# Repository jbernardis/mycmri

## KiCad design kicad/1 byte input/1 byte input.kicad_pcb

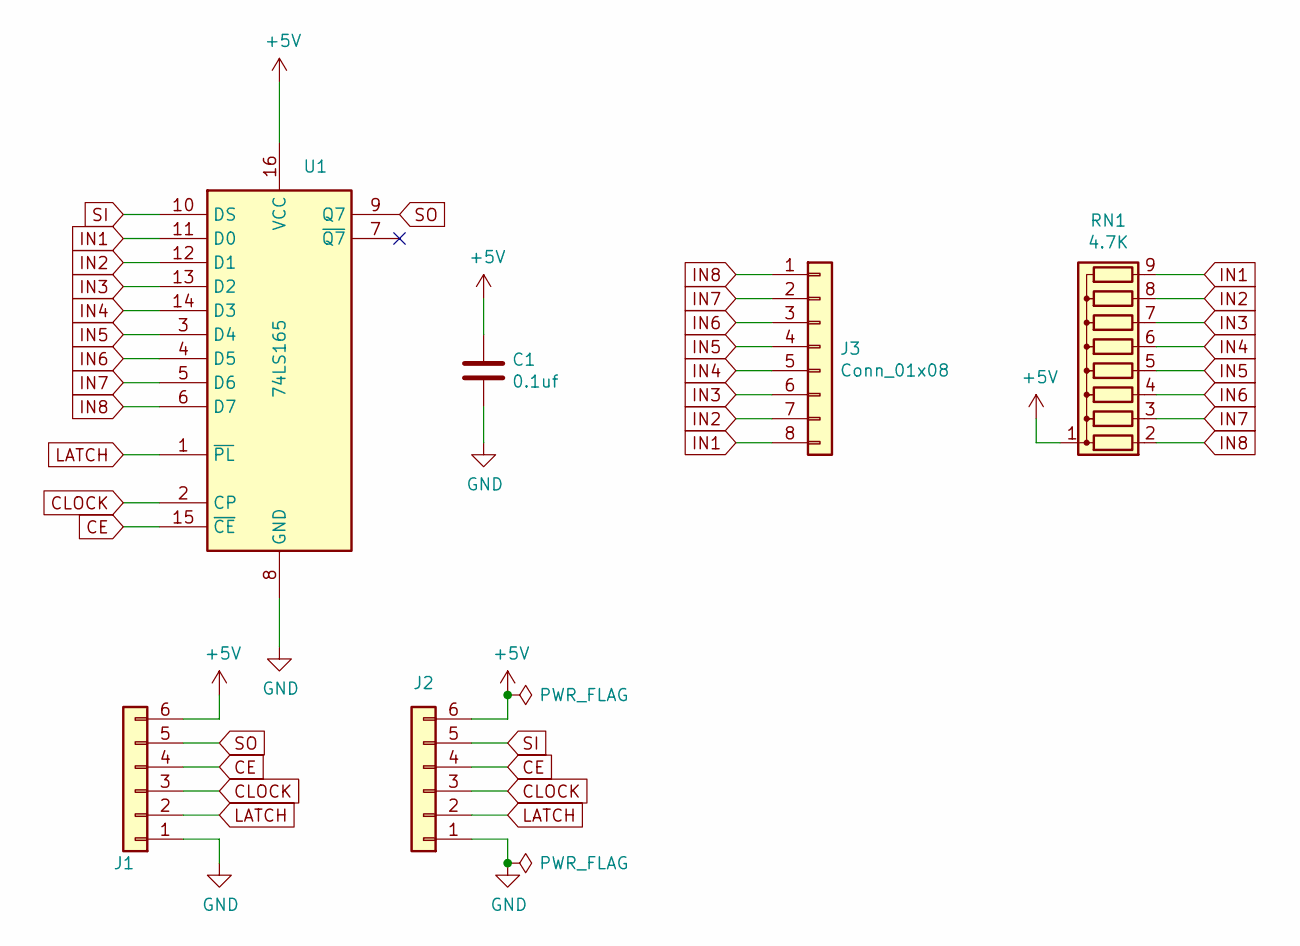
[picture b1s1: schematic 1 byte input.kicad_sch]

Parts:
C1: 0.1uf; C_Disc_D5.0mm_W2.5mm_P2.50mm
J1: Conn_01x06; PinHeader_1x06_P2.54mm_Horizontal
J2: Conn_01x06; PinSocket_1x06_P2.54mm_Horizontal
J3: Conn_01x08; TerminalBlock_Phoenix_MKDS-1,5-8-5.08_1x08_P5.08mm_Horizont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
RN1: 4.7K; R_Array_SIP9
U1: 74LS165; DIP-16_W7.62mm

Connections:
+5V: C1.1, J1.6, J2.6, RN1.1 (common), U1.16 (VCC)
CE: J1.4, J2.4, U1.15 (~CE)
CLOCK: J1.3, J2.3, U1.2 (CP)
GND: C1.2, J1.1, J2.1, U1.8 (GND)
IN1: J3.8, RN1.9 (R8), U1.11 (D0)
IN2: J3.7, RN1.8 (R7), U1.12 (D1)
IN3: J3.6, RN1.7 (R6), U1.13 (D2)
IN4: J3.5, RN1.6 (R5), U1.14 (D3)
IN5: J3.4, RN1.5 (R4), U1.3 (D4)
IN6: J3.3, RN1.4 (R3), U1.4 (D5)
IN7: J3.2, RN1.3 (R2), U1.5 (D6)
IN8: J3.1, RN1.2 (R1), U1.6 (D7)
LATCH: J1.2, J2.2, U1.1 (~PL)
SI: J2.5, U1.10 (DS)
SO: J1.5, U1.9 (Q7)

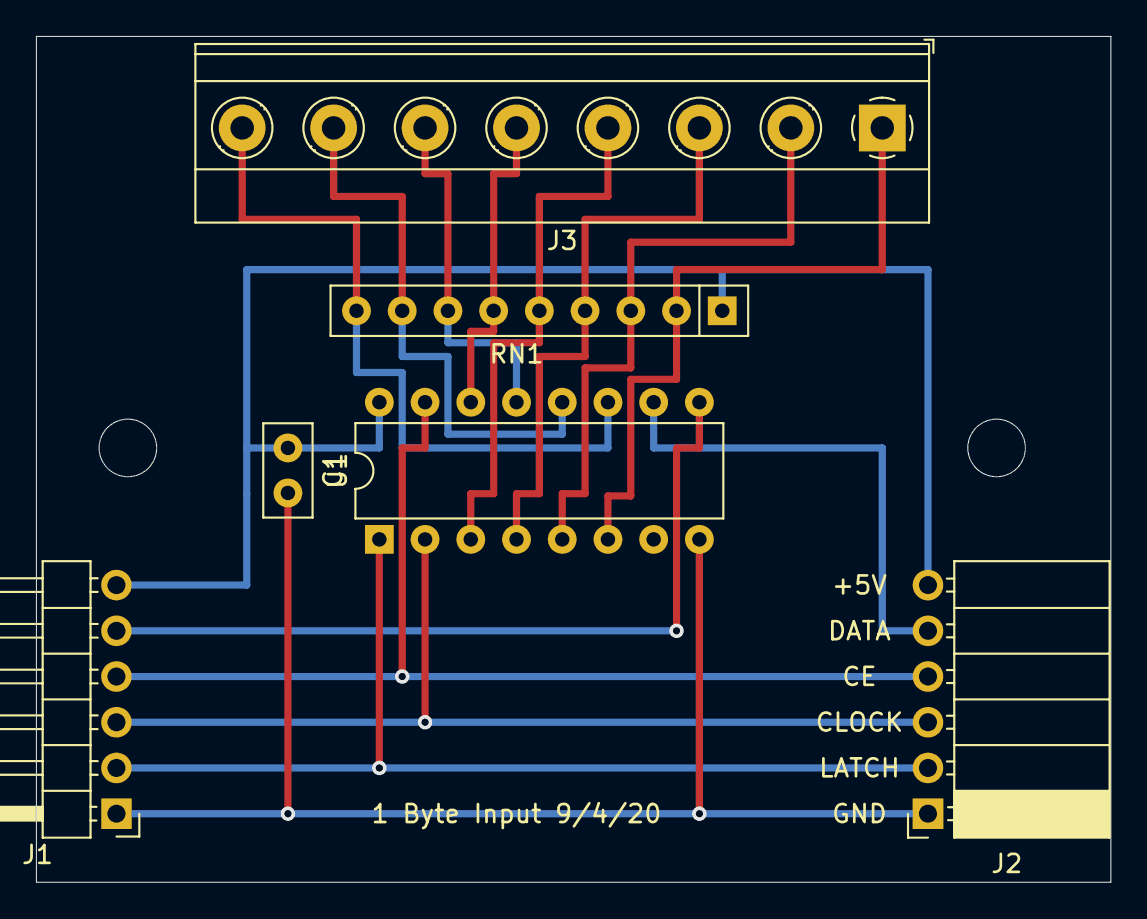
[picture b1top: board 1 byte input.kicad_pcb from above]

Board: 2 copper layers, 59.7 x 47.0 mm, 6 parts (0 on the bottom side), 15 nets.

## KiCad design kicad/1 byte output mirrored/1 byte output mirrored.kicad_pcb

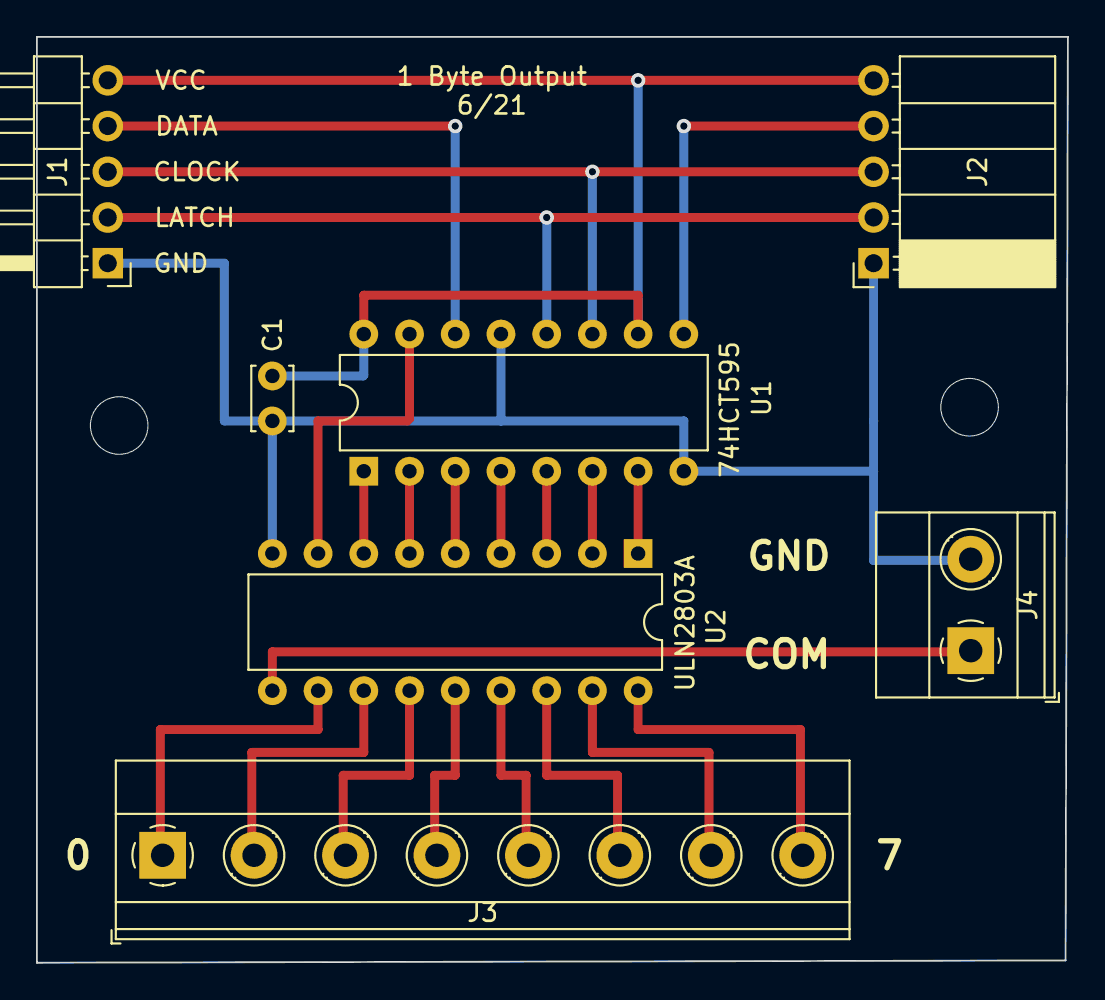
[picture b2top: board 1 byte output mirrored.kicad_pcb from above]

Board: 2 copper layers, 57.3 x 51.4 mm, 9 parts (0 on the bottom side), 23 nets.

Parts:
 : MountingHole_3.2mm_M3
 #2: MountingHole_3.2mm_M3
C1: 0.1uf; C_Disc_D3.4mm_W2.1mm_P2.50mm
J1: Conn_01x05_Male; PinHeader_1x05_P2.54mm_Horizontal
J2: Conn_01x05_Female; PinSocket_1x05_P2.54mm_Horizontal
J3: Conn_01x08; TerminalBlock_Phoenix_MKDS-1,5-8-5.08_1x08_P5.08mm_Horizont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
J4: Screw_Terminal_01x02; TerminalBlock_Phoenix_MKDS-1,5-2-5.08_1x02_P5.08mm_Horizont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
U1: 74HCT595; DIP-16_W7.62mm
U2: ULN2803A; DIP-18_W7.62mm

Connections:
CLK: J1.3, J2.3, U1.11
COM: J4.1, U2.10
DI: J1.4, U1.14
DO: J2.4, U1.9
GND: C1.2, J1.1, J2.1, J4.2, U1.8, U1.13, U2.9
I1: U1.7, U2.1
I2: U1.6, U2.2
I3: U1.5, U2.3
I4: U1.4, U2.4
I5: U1.3, U2.5
I6: U1.2, U2.6
I7: U1.1, U2.7
I8: U1.15, U2.8
LAT: J1.2, J2.2, U1.12
OUT1: J3.1, U2.11
OUT2: J3.2, U2.12
OUT3: J3.3, U2.13
OUT4: J3.4, U2.14
OUT5: J3.5, U2.15
OUT6: J3.6, U2.16
OUT7: J3.7, U2.17
OUT8: J3.8, U2.18
VCC: C1.1, J1.5, J2.5, U1.10, U1.16

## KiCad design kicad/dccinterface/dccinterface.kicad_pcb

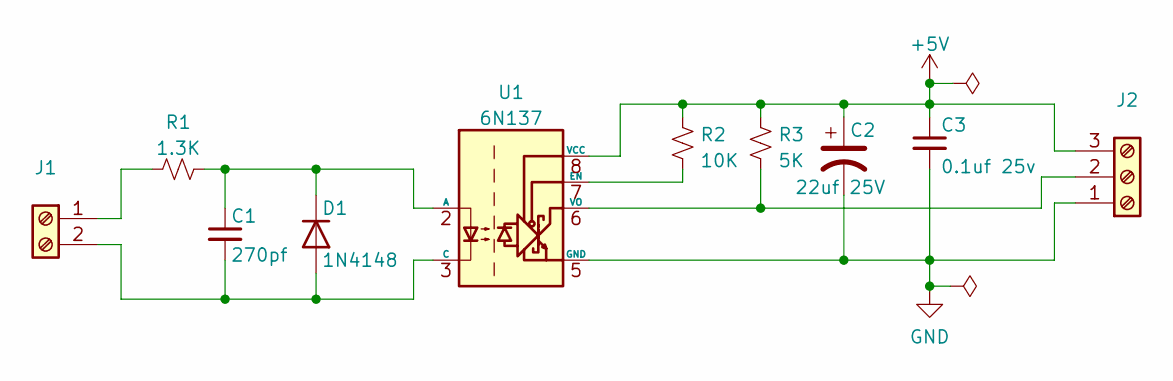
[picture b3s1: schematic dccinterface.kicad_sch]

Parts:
C1: 270pf; C_Disc_D5.0mm_W2.5mm_P2.50mm
C2: 22uf 25V; CP_Radial_D5.0mm_P2.50mm
C3: 0.1uf 25v; C_Disc_D5.0mm_W2.5mm_P2.50mm
D1: 1N4148; D_DO-35_SOD27_P7.62mm_Horizontal
J1: TerminalBlock_Phoenix_MPT-0,5-2-2.54_1x02_P2.54mm_Horizontal
J2: TerminalBlock_Phoenix_MPT-0,5-3-2.54_1x03_P2.54mm_Horizontal
R1: 1.3K; R_Axial_DIN0309_L9.0mm_D3.2mm_P5.08mm_Vertical
R2: 10K; R_Axial_DIN0309_L9.0mm_D3.2mm_P5.08mm_Vertical
R3: 5K; R_Axial_DIN0309_L9.0mm_D3.2mm_P5.08mm_Vertical
U1: 6N137; DIP-8_W7.62mm

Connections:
+5V: C2.1, C3.1, J2.3, R2.1, R3.1, U1.8 (VCC)
GND: C2.2, C3.2, J2.1, U1.5 (GND)
unnamed: J1.1, R1.1
unnamed: C1.1, D1.1 (K), R1.2, U1.2 (A)
unnamed: C1.2, D1.2 (A), J1.2, U1.3 (C)
unnamed: J2.2, R3.2, U1.6 (VO)
unnamed: R2.2, U1.7 (EN)

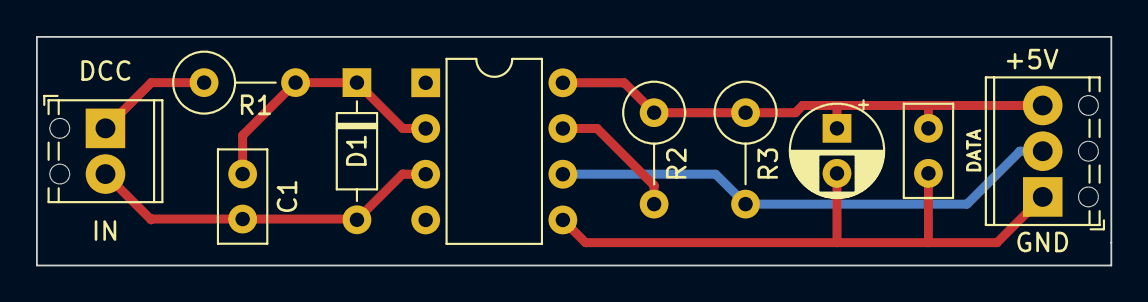
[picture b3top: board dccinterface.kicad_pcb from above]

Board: 2 copper layers, 59.7 x 12.7 mm, 10 parts (0 on the bottom side), 7 nets.

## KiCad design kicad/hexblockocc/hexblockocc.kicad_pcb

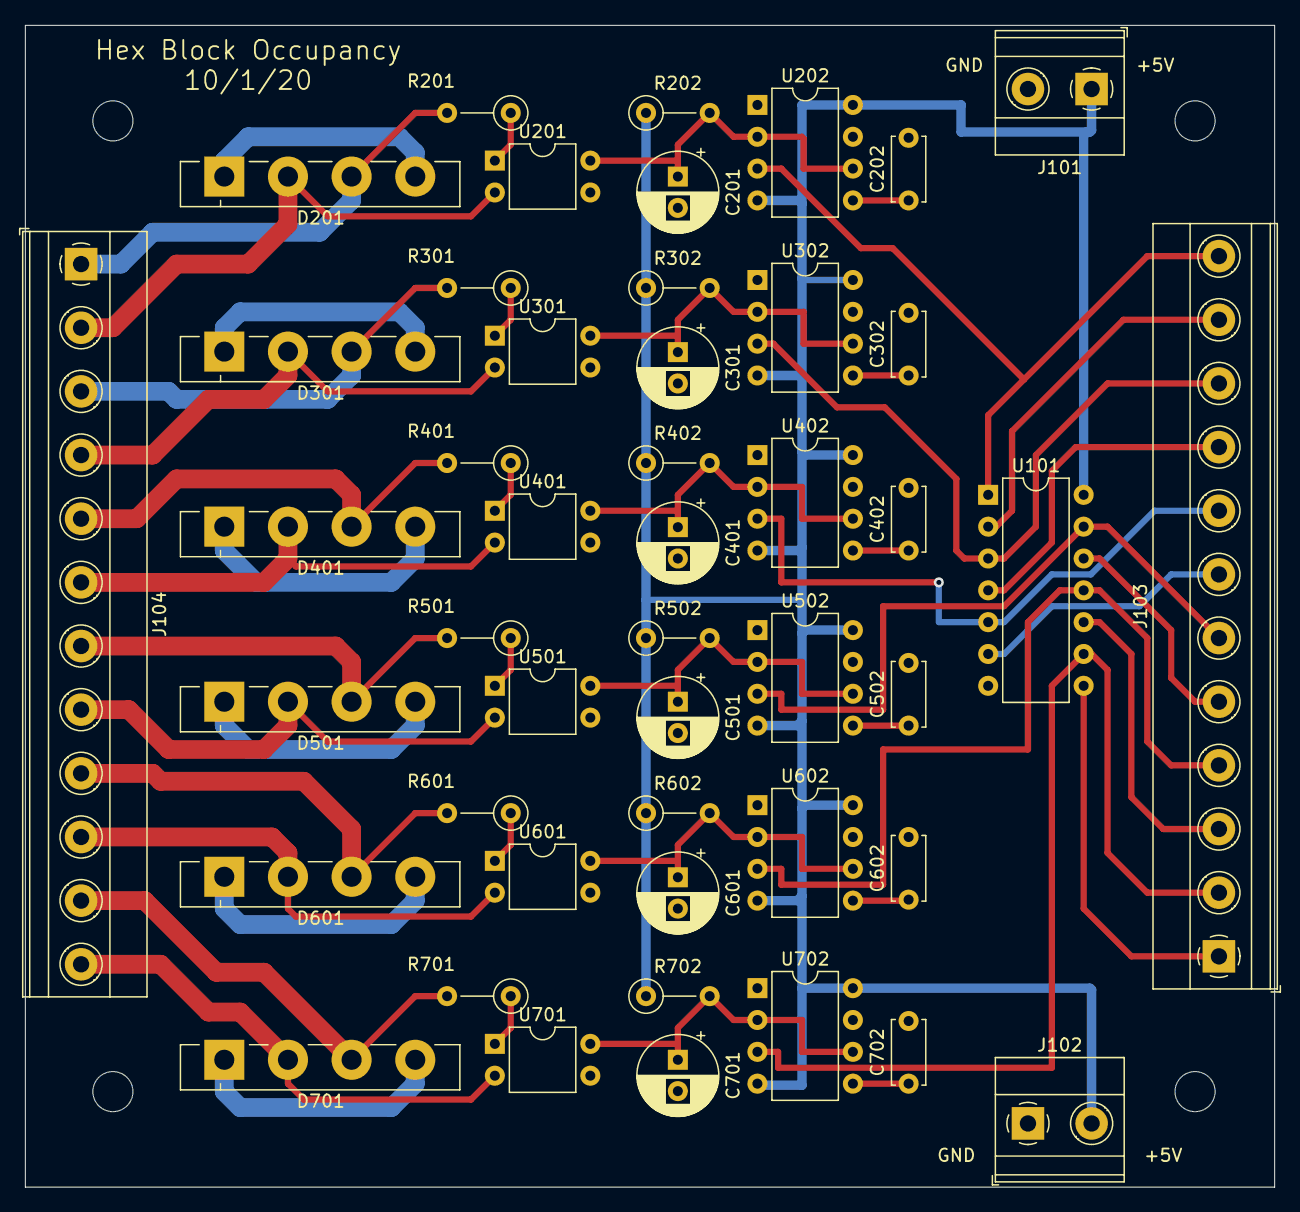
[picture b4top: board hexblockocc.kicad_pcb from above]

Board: 2 copper layers, 99.7 x 92.7 mm, 51 parts (0 on the bottom side), 50 nets.

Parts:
 : MountingHole_3.2mm_M3
 #2,  #3,  #4: MountingHole_3.2mm_M3
C201, C301, C401, C501, C601, C701: 10uf 50v; CP_Radial_D6.3mm_P2.50mm
C202, C302, C402, C502, C602, C702: 0.01uf; C_Disc_D5.0mm_W2.5mm_P5.00mm
D201, D301, D401, D501, D601, D701: GBU4M; Diode_Bridge_Vishay_GBU
J101, J102: Conn_01x02; TerminalBlock_Phoenix_MKDS-1,5-2-5.08_1x02_P5.08mm_Horizont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
J103, J104: Conn_01x12; TerminalBlock_Phoenix_MKDS-1,5-12-5.08_1x12_P5.08mm_Horizon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
R201, R301, R401, R501, R601, R701: 33R; R_Axial_DIN0207_L6.3mm_D2.5mm_P5.08mm_Vertical
R202, R302, R402, R502, R602, R702: 120K; R_Axial_DIN0207_L6.3mm_D2.5mm_P5.08mm_Vertical
U101: 74LS14; DIP-14_W7.62mm
U201, U301, U401, U501, U601, U701: LTV8141; DIP-4_W7.62mm
U202, U302, U402, U502, U602, U702: NE555; DIP-8_W7.62mm

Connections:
+5V: J101.1, J102.2, R202.1, R302.1, R402.1, R502.1, R602.1, R702.1, U101.14, U202.4, U202.8, U302.4, U302.8, U402.4, U402.8, U502.4, U502.8, U602.4, U602.8, U702.4, U702.8
/detection a/DCCINA: D201.3, J104.1, R201.2
/detection a/DCCINB: D201.2, J104.2, U201.2
/detection a/OUT: J103.12, U101.1, U202.3
/detection b/DCCINA: D301.3, J104.3, R301.2
/detection b/DCCINB: D301.2, J104.4, U301.2
/detection b/OUT: J103.10, U101.3, U302.3
/detection c/DCCINA: D401.3, J104.5, R401.2
/detection c/DCCINB: D401.2, J104.6, U401.2
/detection c/OUT: J103.8, U101.5, U402.3
/detection d/DCCINA: D501.3, J104.7, R501.2
/detection d/DCCINB: D501.2, J104.8, U501.2
/detection d/OUT: J103.6, U101.13, U502.3
/detection e/DCCINA: D601.3, J104.9, R601.2
/detection e/DCCINB: D601.2, J104.10, U601.2
/detection e/OUT: J103.4, U101.11, U602.3
/detection f/DCCINA: D701.3, J104.11, R701.2
/detection f/DCCINB: D701.2, J104.12, U701.2
/detection f/OUT: J103.2, U101.9, U702.3
GND: C201.2, C202.2, C301.2, C302.2, C401.2, C402.2, C501.2, C502.2, C601.2, C602.2, C701.2, C702.2, J101.2, J102.1, U101.7, U201.3, U202.1, U301.3, U302.1, U401.3, U402.1, U501.3, U502.1, U601.3, U602.1, U701.3, U702.1
unnamed: C201.1, R202.2, U201.4, U202.2, U202.6
unnamed: C202.1, U202.5
unnamed: C301.1, R302.2, U301.4, U302.2, U302.6
unnamed: C302.1, U302.5
unnamed: C401.1, R402.2, U401.4, U402.2, U402.6
unnamed: C402.1, U402.5
unnamed: C501.1, R502.2, U501.4, U502.2, U502.6
unnamed: C502.1, U502.5
unnamed: C601.1, R602.2, U601.4, U602.2, U602.6
unnamed: C602.1, U602.5
unnamed: C701.1, R702.2, U701.4, U702.2, U702.6
unnamed: C702.1, U702.5
unnamed: D201.1, D201.4
unnamed: D301.1, D301.4
unnamed: D401.1, D401.4
unnamed: D501.1, D501.4
unnamed: D601.1, D601.4
unnamed: D701.1, D701.4
unnamed: J103.1, U101.8
unnamed: J103.3, U101.10
unnamed: J103.5, U101.12
unnamed: J103.7, U101.6
unnamed: J103.9, U101.4
unnamed: J103.11, U101.2
unnamed: R201.1, U201.1
unnamed: R301.1, U301.1
unnamed: R401.1, U401.1
unnamed: R501.1, U501.1
unnamed: R601.1, U601.1
unnamed: R701.1, U701.1
